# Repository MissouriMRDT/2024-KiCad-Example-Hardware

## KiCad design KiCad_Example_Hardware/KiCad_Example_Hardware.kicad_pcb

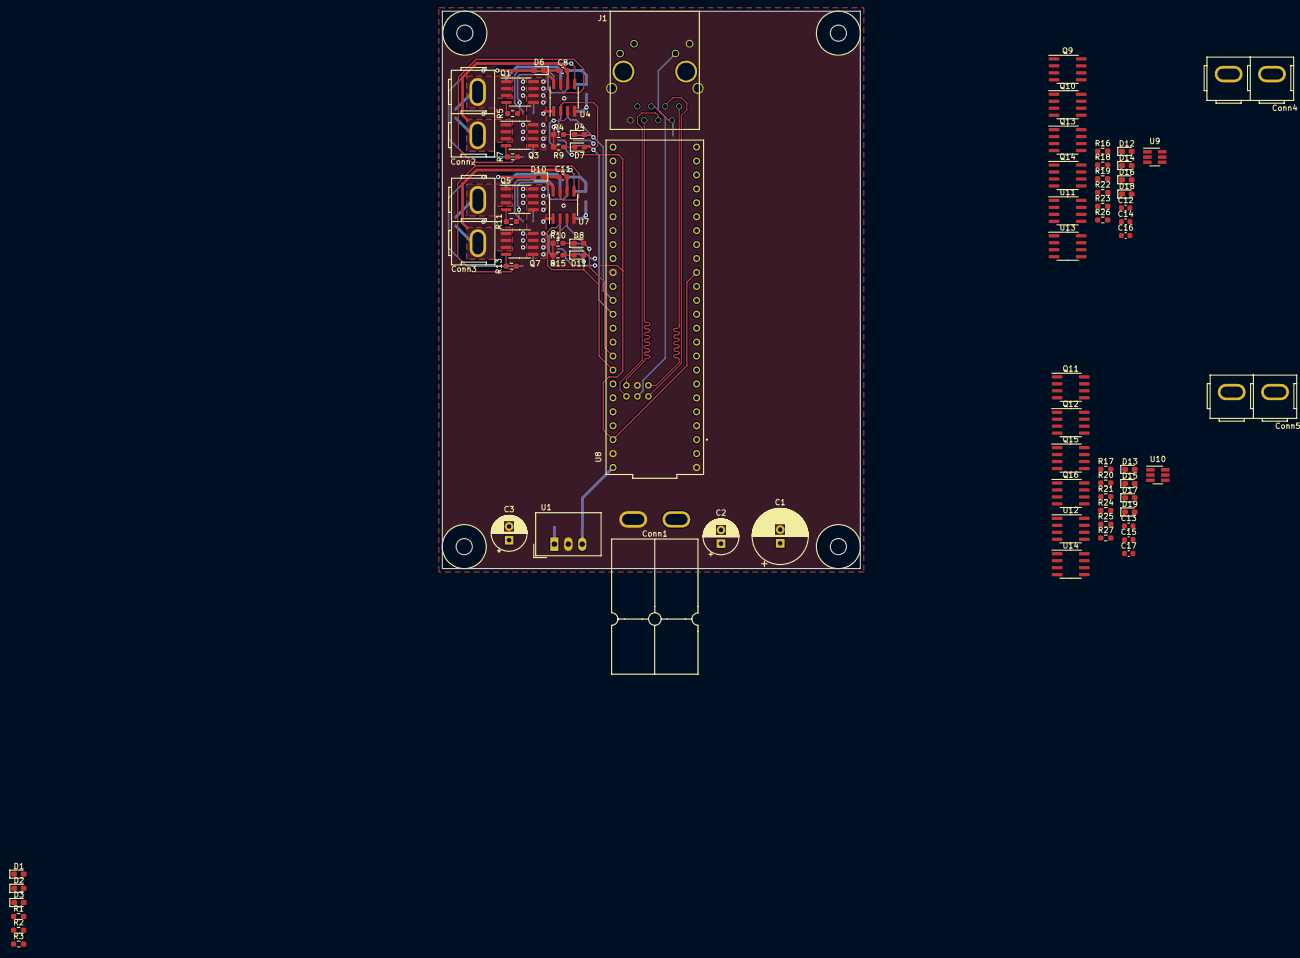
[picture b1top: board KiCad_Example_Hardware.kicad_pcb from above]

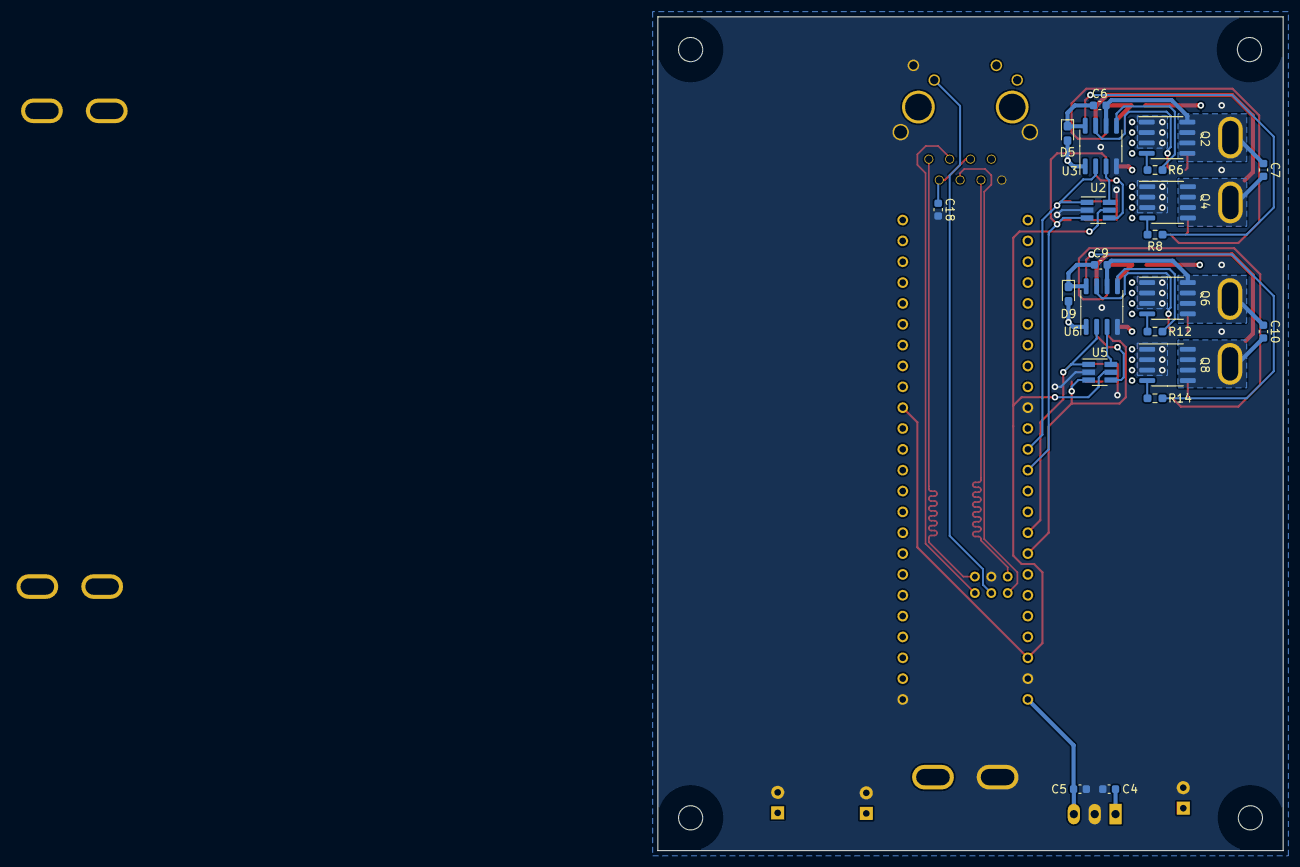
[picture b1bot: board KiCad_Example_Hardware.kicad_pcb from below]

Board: 4 copper layers, 76.2 x 101.6 mm, 104 parts (21 on the bottom side), 85 nets.

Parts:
C1: 470uF; CP_Radial_D10.0mm_P2.50mm
C2: 220uF; CP_Radial_D6.3mm_P2.50mm
C3: 100uF; CP_Radial_D6.3mm_P2.50mm
C4, C5, C7, C10, C14, C15: 10u; C_0603_1608Metric
C6, C8, C9, C11, C12, C13, C16, C17: 1u; C_0603_1608Metric
C18: 0.1uF; C_0603_1608Metric
Conn1: AndersonPP; Square_Anderson_2_H_Side_By_Side
Conn2, Conn3, Conn4, Conn5: AndersonPP; Square_Anderson_2_V_Side_By_Side
D1, D2, D3: Green; LED_0603_1608Metric_Pad1.05x0.95mm_HandSolder
D4, D7, D8, D11, D12, D13, D18, D19: Orange; LED_0603_1608Metric_Pad1.05x0.95mm_HandSolder
D5, D6, D9, D10, D14, D15, D16, D17: D_Small; LED_0603_1608Metric_Pad1.05x0.95mm_HandSolder
H1, H2, H3, H4: MountingHole; 4_40_Hole_Corner
J1: RJ45_LED_Shielded; RJ45_Teensy
Q1, Q2, Q3, Q4, Q5, Q6, Q7, Q8, Q9, Q10, Q11, Q12, Q13, Q14, Q15, Q16: SI4156DY; SOIC-8_3.9x4.9mm_P1.27mm
R1: 1k; R_0603_1608Metric_Pad0.98x0.95mm_HandSolder
R2: 300; R_0603_1608Metric_Pad0.98x0.95mm_HandSolder
R3, R4, R9, R10, R15, R16, R17, R26, R27: 120; R_0603_1608Metric_Pad0.98x0.95mm_HandSolder
R5, R6, R7, R8, R11, R12, R13, R14, R18, R19, R20, R21, R22, R23, R24, R25: 100; R_0603_1608Metric_Pad0.98x0.95mm_HandSolder
U1: TSR_1-2450; Converter_DCDC_TRACO_TSR-1_THT
U2, U5, U9, U10: 74LVC2G04; SOT-23-6_Handsoldering
U3, U4, U6, U7, U11, U12, U13, U14: IRS2005S; SOIC-8_3.9x4.9mm_P1.27mm
U8: Teensy4.1_DEV-16771; Teensy_4_1_Ethernet

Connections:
+3V3: D3.2 (A), U2.5 (VCC), U5.5 (VCC), U8.3.3V_1 (3.3V), U8.3.3V_2 (3.3V), U9.5 (VCC), U10.5 (VCC)
+5V: C5.1, D2.2 (A), U1.3 (Vout), U8.VIN
+12V: C1.1, C2.1, C3.1, C4.1, Conn1.2 (V+Log), D1.2 (A), D5.2 (A), D6.2 (A), D9.2 (A), D10.2 (A), D14.2 (A), D15.2 (A), D16.2 (A), D17.2 (A), Q1.5 (D), Q1.6 (D), Q1.7 (D), Q1.8 (D), Q3.5 (D), Q3.6 (D), Q3.7 (D), Q3.8 (D), Q5.5 (D), Q5.6 (D), Q5.7 (D), Q5.8 (D), Q7.5 (D), Q7.6 (D), Q7.7 (D), Q7.8 (D), Q9.5 (D), Q9.6 (D), Q9.7 (D), Q9.8 (D), Q11.5 (D), Q11.6 (D), Q11.7 (D), Q11.8 (D), Q13.5 (D), Q13.6 (D), Q13.7 (D), Q13.8 (D), Q15.5 (D), Q15.6 (D), Q15.7 (D), Q15.8 (D), U1.1 (Vin), U3.1 (VCC), U4.1 (VCC), U6.1 (VCC), U7.1 (VCC), U11.1 (VCC), U12.1 (VCC), U13.1 (VCC), U14.1 (VCC)
/FWD_PWM_1: D4.2 (A), U2.1, U3.2 (HIN), U8.14 (A0)
/FWD_PWM_2: D8.2 (A), U5.1, U6.2 (HIN), U8.18 (A4)
/FWD_PWM_3: D12.2 (A), U8.28 (RX7), U9.1, U11.2 (HIN)
/FWD_PWM_4: D13.2 (A), U8.25 (A11), U10.1, U12.2 (HIN)
/Motor Controllers 2/3M+: C12.2, C14.1, Conn4.1 (GND), Q9.1 (S), Q9.2 (S), Q9.3 (S), Q10.5 (D), Q10.6 (D), Q10.7 (D), Q10.8 (D), U11.6 (VS)
/Motor Controllers 2/3M-: C14.2, C16.2, Conn4.2 (V+Log), Q13.1 (S), Q13.2 (S), Q13.3 (S), Q14.5 (D), Q14.6 (D), Q14.7 (D), Q14.8 (D), U13.6 (VS)
/Motor Controllers 2/4M+: C13.2, C15.1, Conn5.1 (GND), Q11.1 (S), Q11.2 (S), Q11.3 (S), Q12.5 (D), Q12.6 (D), Q12.7 (D), Q12.8 (D), U12.6 (VS)
/Motor Controllers 2/4M-: C15.2, C17.2, Conn5.2 (V+Log), Q15.1 (S), Q15.2 (S), Q15.3 (S), Q16.5 (D), Q16.6 (D), Q16.7 (D), Q16.8 (D), U14.6 (VS)
/Motor Controllers/1M+: C6.2, C7.1, Conn2.1 (GND), Q1.1 (S), Q1.2 (S), Q1.3 (S), Q2.5 (D), Q2.6 (D), Q2.7 (D), Q2.8 (D), U3.6 (VS)
/Motor Controllers/1M-: C7.2, C8.2, Conn2.2 (V+Log), Q3.1 (S), Q3.2 (S), Q3.3 (S), Q4.5 (D), Q4.6 (D), Q4.7 (D), Q4.8 (D), U4.6 (VS)
/Motor Controllers/2M+: C9.2, C10.1, Conn3.1 (GND), Q5.1 (S), Q5.2 (S), Q5.3 (S), Q6.5 (D), Q6.6 (D), Q6.7 (D), Q6.8 (D), U6.6 (VS)
/Motor Controllers/2M-: C10.2, C11.2, Conn3.2 (V+Log), Q7.1 (S), Q7.2 (S), Q7.3 (S), Q8.5 (D), Q8.6 (D), Q8.7 (D), Q8.8 (D), U7.6 (VS)
/RVS_PWM_1: D7.2 (A), U2.3, U4.2 (HIN), U8.15 (A1)
/RVS_PWM_2: D11.2 (A), U5.3, U7.2 (HIN), U8.19 (A5)
/RVS_PWM_3: D18.2 (A), U8.29 (TX7), U9.3, U13.2 (HIN)
/RVS_PWM_4: D19.2 (A), U8.24 (A10), U10.3, U14.2 (HIN)
GND: C1.2, C2.2, C3.2, C4.2, C5.2, C18.2, Conn1.1 (GND), J1.8, J1.9, J1.SH, Q2.1 (S), Q2.2 (S), Q2.3 (S), Q4.1 (S), Q4.2 (S), Q4.3 (S), Q6.1 (S), Q6.2 (S), Q6.3 (S), Q8.1 (S), Q8.2 (S), Q8.3 (S), Q10.1 (S), Q10.2 (S), Q10.3 (S), Q12.1 (S), Q12.2 (S), Q12.3 (S), Q14.1 (S), Q14.2 (S), Q14.3 (S), Q16.1 (S), Q16.2 (S), Q16.3 (S), R1.2, R2.2, R3.2, R4.2, R9.1, R10.2, R15.1, R16.2, R17.2, R26.1, R27.1, U1.2 (GND), U2.2 (GND), U3.4 (COM), U4.4 (COM), U5.2 (GND), U6.4 (COM), U7.4 (COM), U8.GND1 (GND), U8.GND2 (GND), U8.GND3 (GND), U8.GND5 (GND), U9.2 (GND), U10.2 (GND), U11.4 (COM), U12.4 (COM), U13.4 (COM), U14.4 (COM)
LED: J1.10, U8.LED
unnamed: C18.1, J1.2, J1.5
unnamed: D1.1 (K), R1.1
unnamed: D2.1 (K), R2.1
unnamed: D3.1 (K), R3.1
unnamed: D4.1 (K), R4.1
unnamed: C6.1, D5.1 (K), U3.8 (VB)
unnamed: C8.1, D6.1 (K), U4.8 (VB)
unnamed: D7.1 (K), R9.2
unnamed: D8.1 (K), R10.1
unnamed: C9.1, D9.1 (K), U6.8 (VB)
unnamed: C11.1, D10.1 (K), U7.8 (VB)
unnamed: D11.1 (K), R15.2
unnamed: D12.1 (K), R16.1
unnamed: D13.1 (K), R17.1
unnamed: C12.1, D14.1 (K), U11.8 (VB)
unnamed: C13.1, D15.1 (K), U12.8 (VB)
unnamed: C16.1, D16.1 (K), U13.8 (VB)
unnamed: C17.1, D17.1 (K), U14.8 (VB)
unnamed: D18.1 (K), R26.2
unnamed: D19.1 (K), R27.2
unnamed: Q1.4 (G), R5.2
unnamed: Q2.4 (G), R6.2
unnamed: Q3.4 (G), R7.2
unnamed: Q4.4 (G), R8.2
unnamed: Q5.4 (G), R11.2
unnamed: Q6.4 (G), R12.2
unnamed: Q7.4 (G), R13.2
unnamed: Q8.4 (G), R14.2
unnamed: Q9.4 (G), R18.2
unnamed: Q10.4 (G), R19.2
unnamed: Q11.4 (G), R20.2
unnamed: Q12.4 (G), R21.2
unnamed: Q13.4 (G), R22.2
unnamed: Q14.4 (G), R23.2
unnamed: Q15.4 (G), R24.2
unnamed: Q16.4 (G), R25.2
unnamed: R5.1, U3.7 (HO)
unnamed: U2.6, U3.3 (LIN)
unnamed: R6.1, U3.5 (LO)
unnamed: R7.1, U4.7 (HO)
unnamed: U2.4, U4.3 (LIN)
unnamed: R8.1, U4.5 (LO)
unnamed: R11.1, U6.7 (HO)
unnamed: U5.6, U6.3 (LIN)
unnamed: R12.1, U6.5 (LO)
unnamed: R13.1, U7.7 (HO)
unnamed: U5.4, U7.3 (LIN)
unnamed: R14.1, U7.5 (LO)
unnamed: R18.1, U11.7 (HO)
unnamed: U9.6, U11.3 (LIN)
unnamed: R19.1, U11.5 (LO)
unnamed: R20.1, U12.7 (HO)
unnamed: U10.6, U12.3 (LIN)
unnamed: R21.1, U12.5 (LO)
unnamed: R22.1, U13.7 (HO)
unnamed: U9.4, U13.3 (LIN)
unnamed: R23.1, U13.5 (LO)
unnamed: R24.1, U14.7 (HO)
unnamed: U10.4, U14.3 (LIN)
unnamed: R25.1, U14.5 (LO)
Rx+: J1.4, U8.R+
Rx-: J1.6, U8.R-
Tx+: J1.1, U8.T+
Tx-: J1.3, U8.T-

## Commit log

2023-07-01 Schematic + Started layout
2023-07-01 Finished 2nd H bridge
